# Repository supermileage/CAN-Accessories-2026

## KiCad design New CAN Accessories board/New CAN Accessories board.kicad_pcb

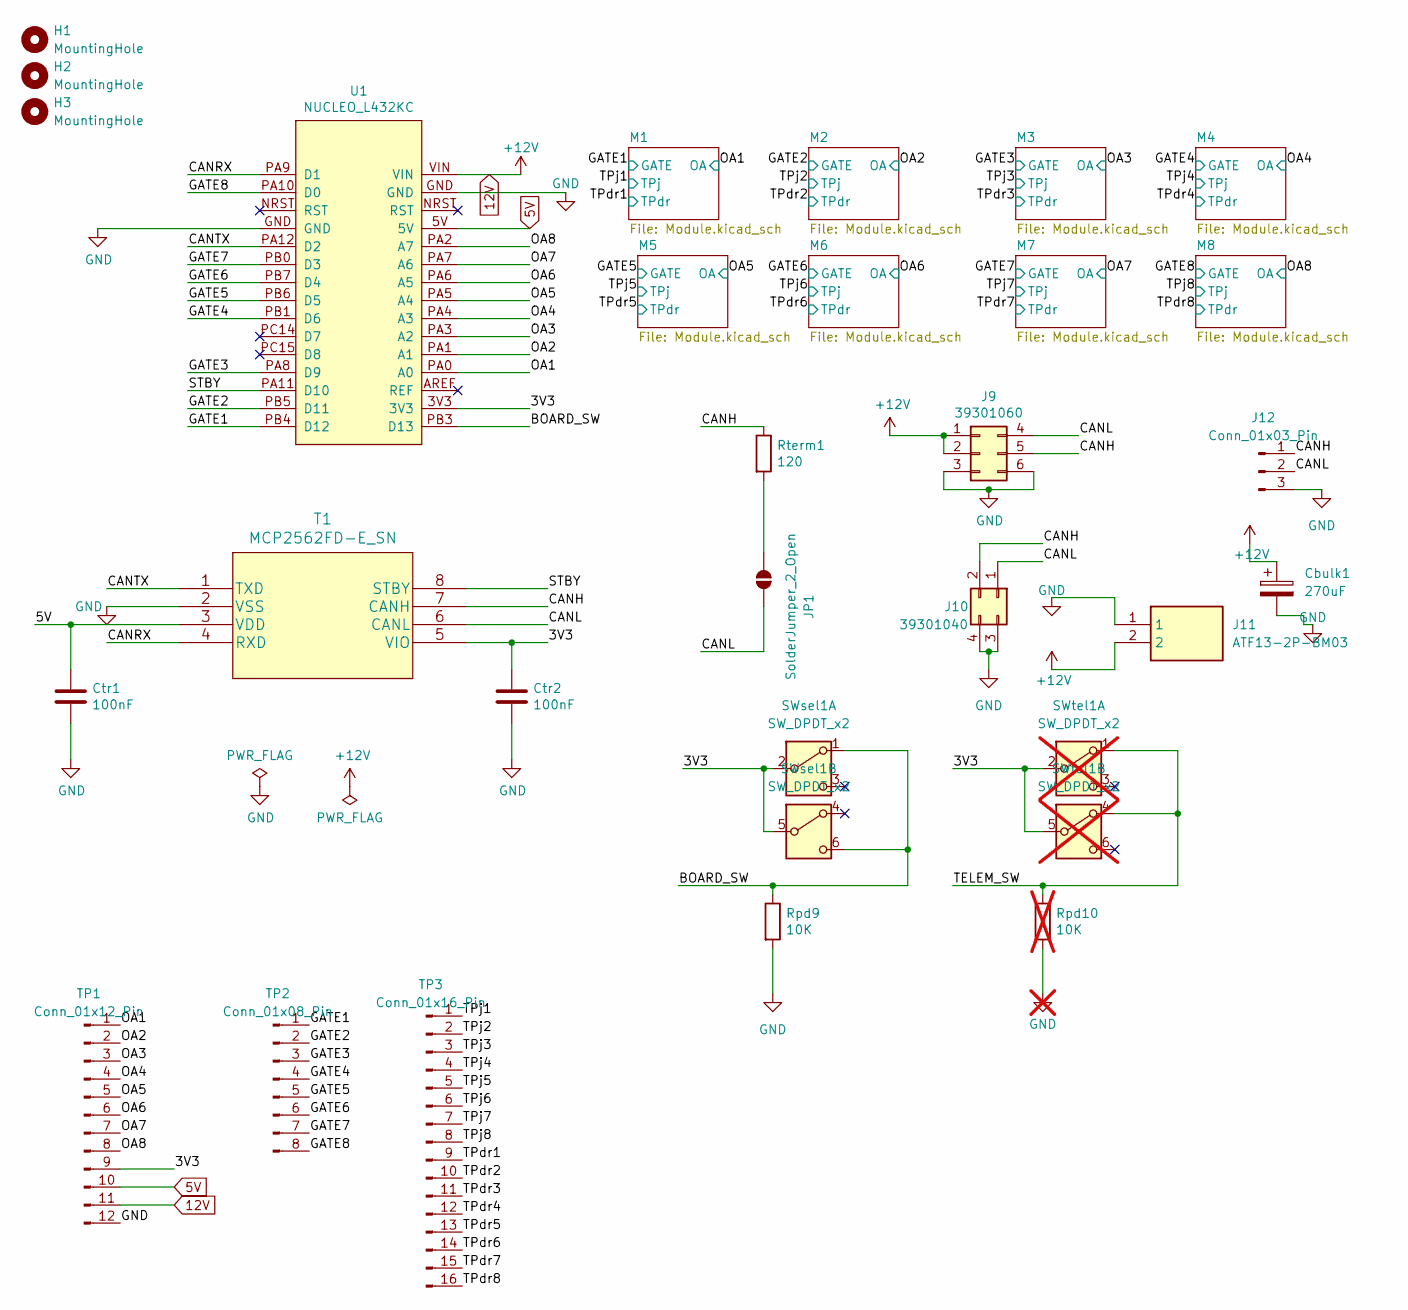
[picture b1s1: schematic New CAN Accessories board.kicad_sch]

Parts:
Cbulk1: 270uF; CAPAE1030X1050M
Ctr1, Ctr2: 100nF; C_0805_2012Metric
H1, H2, H3: MountingHole; MountingHole_3.2mm_M3_ISO14580
J9: 39301060; Molex_Mini-Fit_Jr_5569-06A2_2x03_P4.20mm_Horizontal
J10: 39301040; Molex_Mini-Fit_Jr_5569-04A2_2x02_P4.20mm_Horizontal
J11: ATF13-2P-BM03; ATF132PBM03; Mouser Part Number 654-ATF13-2P-BM03
J12: Conn_01x03_Pin; PinHeader_1x03_P2.54mm_Vertical
JP1: SolderJumper_2_Open; SolderJumper-2_P1.3mm_Open_Pad1.0x1.5mm
Rpd9: 10K; R_0805_2012Metric
Rpd10: 10K; R_0805_2012Metric; not fitted
Rterm1: 120; R_0805_2012Metric
SWsel1: SW_DPDT_x2; SWITCH_011CQN
SWtel1: SW_DPDT_x2; SWITCH_011CQN; not fitted
T1: MCP2562FD-E_SN; SOIC-8_3.9x4.9mm_P1.27mm
TP1: Conn_01x12_Pin; PinHeader_1x12_P2.54mm_Vertical
TP2: Conn_01x08_Pin; PinHeader_1x08_P2.54mm_Vertical
TP3: Conn_01x16_Pin; PinHeader_1x16_P2.54mm_Vertical
U1: NUCLEO_L432KC; MODULE_NUCLEO-L432KC

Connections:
5V: Ctr1.1, T1.3 (VDD), TP1.10, U1.5V; also elsewhere on the board
12V: Cbulk1.1, J9.1, J9.2, J11.2, TP1.11, U1.VIN; also elsewhere on the board
/3V3: Ctr2.1, SWsel1.2 (B), SWsel1.5 (B), SWtel1.2 (B), SWtel1.5 (B), T1.5 (VIO), TP1.9, U1.3V3
/BOARD_SW: Rpd9.1, SWsel1.1 (A), SWsel1.6 (C), U1.PB3 (D13)
/CANH: J9.5, J10.2, J12.1, Rterm1.1, T1.7 (CANH)
/CANL: J9.4, J10.1, J12.2, JP1.2 (B), T1.6 (CANL)
/CANRX: T1.4 (RXD), U1.PA9 (D1)
/CANTX: T1.1 (TXD), U1.PA12 (D2)
/GATE1: TP2.1, U1.PB4 (D12); also elsewhere on the board
/GATE2: TP2.2, U1.PB5 (D11); also elsewhere on the board
/GATE3: TP2.3, U1.PA8 (D9); also elsewhere on the board
/GATE4: TP2.4, U1.PB1 (D6); also elsewhere on the board
/GATE5: TP2.5, U1.PB6 (D5); also elsewhere on the board
/GATE6: TP2.6, U1.PB7 (D4); also elsewhere on the board
/GATE7: TP2.7, U1.PB0 (D3); also elsewhere on the board
/GATE8: TP2.8, U1.PA10 (D0); also elsewhere on the board
/OA1: TP1.1, U1.PA0 (A0); also elsewhere on the board
/OA2: TP1.2, U1.PA1 (A1); also elsewhere on the board
/OA3: TP1.3, U1.PA3 (A2); also elsewhere on the board
/OA4: TP1.4, U1.PA4 (A3); also elsewhere on the board
/OA5: TP1.5, U1.PA5 (A4); also elsewhere on the board
/OA6: TP1.6, U1.PA6 (A5); also elsewhere on the board
/OA7: TP1.7, U1.PA7 (A6); also elsewhere on the board
/OA8: TP1.8, U1.PA2 (A7); also elsewhere on the board
/STBY: T1.8 (STBY), U1.PA11 (D10)
/TPdr1: TP3.9; also elsewhere on the board
/TPdr2: TP3.10; also elsewhere on the board
/TPdr3: TP3.11; also elsewhere on the board
/TPdr4: TP3.12; also elsewhere on the board
/TPdr5: TP3.13; also elsewhere on the board
/TPdr6: TP3.14; also elsewhere on the board
/TPdr7: TP3.15; also elsewhere on the board
/TPdr8: TP3.16; also elsewhere on the board
/TPj1: TP3.1; also elsewhere on the board
/TPj2: TP3.2; also elsewhere on the board
/TPj3: TP3.3; also elsewhere on the board
/TPj4: TP3.4; also elsewhere on the board
/TPj5: TP3.5; also elsewhere on the board
/TPj6: TP3.6; also elsewhere on the board
/TPj7: TP3.7; also elsewhere on the board
/TPj8: TP3.8; also elsewhere on the board
GND: Cbulk1.2, Ctr1.2, Ctr2.2, J9.3, J9.6, J10.3, J10.4, J11.1, J12.3, Rpd9.2, Rpd10.2, T1.2 (VSS), TP1.12, U1.GND; also elsewhere on the board
unnamed: JP1.1 (A), Rterm1.2
unnamed: Rpd10.1, SWtel1.1 (A), SWtel1.4 (A)

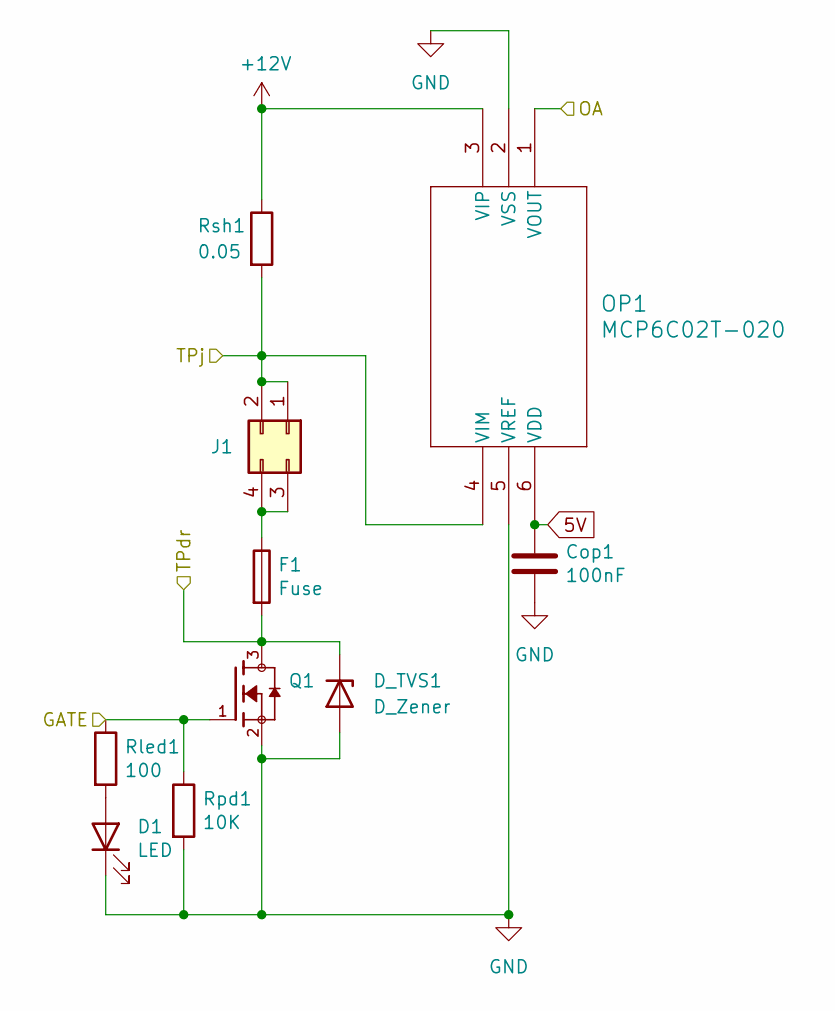
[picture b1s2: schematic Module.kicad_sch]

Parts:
Cop1: 100nF; C_0805_2012Metric
D1: LED; LED_0805_2012Metric
D_TVS1: D_Zener; D_SMF
F1: Fuse; 3586KTR
J1: 39301040; Molex_Mini-Fit_Jr_5569-04A2_2x02_P4.20mm_Horizontal
OP1: MCP6C02T-020; SOT-23-6_Handsoldering
Q1: IRLML6344TRPBF; TSOT-23; PARTREV December 19, 2014
Rled1: 100; R_0805_2012Metric
Rpd1: 10K; R_0805_2012Metric
Rsh1: 0.05; R_2512_6332Metric_Pad1.40x3.35mm_HandSolder

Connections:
5V: Cop1.1, OP1.6 (VDD); also elsewhere on the board
12V: OP1.3 (VIP), Rsh1.1; also elsewhere on the board
/GATE1: Q1.1, Rled1.1, Rpd1.1; also elsewhere on the board
/OA1: OP1.1 (VOUT); also elsewhere on the board
/TPdr1: D_TVS1.1 (K), F1.2, Q1.3; also elsewhere on the board
/TPj1: J1.1, J1.2, OP1.4 (VIM), Rsh1.2; also elsewhere on the board
GND: Cop1.2, D1.1 (K), D_TVS1.2 (A), OP1.2 (VSS), OP1.5 (VREF), Q1.2, Rpd1.2; also elsewhere on the board
unnamed: D1.2 (A), Rled1.2
unnamed: F1.1, J1.3, J1.4

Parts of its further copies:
Cop2, Cop3, Cop4, Cop5, Cop6, Cop7, Cop8: 100nF; C_0805_2012Metric
D2, D3, D4, D5, D6, D7, D8: LED; LED_0805_2012Metric
D_TVS2, D_TVS3, D_TVS4, D_TVS5, D_TVS6, D_TVS7, D_TVS8: D_Zener; D_SMF
F2, F3, F4, F5, F6, F7, F8: Fuse; 3586KTR
J2, J3, J4, J5, J6, J7, J8: 39301040; Molex_Mini-Fit_Jr_5569-04A2_2x02_P4.20mm_Horizontal
OP2, OP3, OP4, OP5, OP6, OP7, OP8: MCP6C02T-020; SOT-23-6_Handsoldering
Q2, Q3, Q4, Q5, Q6, Q7, Q8: IRLML6344TRPBF; TSOT-23; PARTREV December 19, 2014
Rled2, Rled3, Rled4, Rled5, Rled6, Rled7, Rled8: 100; R_0805_2012Metric
Rpd2, Rpd3, Rpd4, Rpd5, Rpd6, Rpd7, Rpd8: 10K; R_0805_2012Metric
Rsh2, Rsh3, Rsh4, Rsh5, Rsh6, Rsh7, Rsh8: 0.05; R_2512_6332Metric_Pad1.40x3.35mm_HandSolder

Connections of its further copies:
5V: Cop2.1, Cop3.1, Cop4.1, Cop5.1, Cop6.1, Cop7.1, Cop8.1, OP2.6 (VDD), OP3.6 (VDD), OP4.6 (VDD), OP5.6 (VDD), OP6.6 (VDD), OP7.6 (VDD), OP8.6 (VDD); also elsewhere on the board
12V: OP2.3 (VIP), OP3.3 (VIP), OP4.3 (VIP), OP5.3 (VIP), OP6.3 (VIP), OP7.3 (VIP), OP8.3 (VIP), Rsh2.1, Rsh3.1, Rsh4.1, Rsh5.1, Rsh6.1, Rsh7.1, Rsh8.1; also elsewhere on the board
/GATE2: Q2.1, Rled2.1, Rpd2.1; also elsewhere on the board
/GATE3: Q3.1, Rled3.1, Rpd3.1; also elsewhere on the board
/GATE4: Q4.1, Rled4.1, Rpd4.1; also elsewhere on the board
/GATE5: Q5.1, Rled5.1, Rpd5.1; also elsewhere on the board
/GATE6: Q6.1, Rled6.1, Rpd6.1; also elsewhere on the board
/GATE7: Q7.1, Rled7.1, Rpd7.1; also elsewhere on the board
/GATE8: Q8.1, Rled8.1, Rpd8.1; also elsewhere on the board
/OA2: OP2.1 (VOUT); also elsewhere on the board
/OA3: OP3.1 (VOUT); also elsewhere on the board
/OA4: OP4.1 (VOUT); also elsewhere on the board
/OA5: OP5.1 (VOUT); also elsewhere on the board
/OA6: OP6.1 (VOUT); also elsewhere on the board
/OA7: OP7.1 (VOUT); also elsewhere on the board
/OA8: OP8.1 (VOUT); also elsewhere on the board
/TPdr2: D_TVS2.1 (K), F2.2, Q2.3; also elsewhere on the board
/TPdr3: D_TVS3.1 (K), F3.2, Q3.3; also elsewhere on the board
/TPdr4: D_TVS4.1 (K), F4.2, Q4.3; also elsewhere on the board
/TPdr5: D_TVS5.1 (K), F5.2, Q5.3; also elsewhere on the board
/TPdr6: D_TVS6.1 (K), F6.2, Q6.3; also elsewhere on the board
/TPdr7: D_TVS7.1 (K), F7.2, Q7.3; also elsewhere on the board
/TPdr8: D_TVS8.1 (K), F8.2, Q8.3; also elsewhere on the board
/TPj2: J2.1, J2.2, OP2.4 (VIM), Rsh2.2; also elsewhere on the board
/TPj3: J3.1, J3.2, OP3.4 (VIM), Rsh3.2; also elsewhere on the board
/TPj4: J4.1, J4.2, OP4.4 (VIM), Rsh4.2; also elsewhere on the board
/TPj5: J5.1, J5.2, OP5.4 (VIM), Rsh5.2; also elsewhere on the board
/TPj6: J6.1, J6.2, OP6.4 (VIM), Rsh6.2; also elsewhere on the board
/TPj7: J7.1, J7.2, OP7.4 (VIM), Rsh7.2; also elsewhere on the board
/TPj8: J8.1, J8.2, OP8.4 (VIM), Rsh8.2; also elsewhere on the board
GND: Cop2.2, Cop3.2, Cop4.2, Cop5.2, Cop6.2, Cop7.2, Cop8.2, D2.1 (K), D3.1 (K), D4.1 (K), D5.1 (K), D6.1 (K), D7.1 (K), D8.1 (K), D_TVS2.2 (A), D_TVS3.2 (A), D_TVS4.2 (A), D_TVS5.2 (A), D_TVS6.2 (A), D_TVS7.2 (A), D_TVS8.2 (A), OP2.2 (VSS), OP2.5 (VREF), OP3.2 (VSS), OP3.5 (VREF), OP4.2 (VSS), OP4.5 (VREF), OP5.2 (VSS), OP5.5 (VREF), OP6.2 (VSS), OP6.5 (VREF), OP7.2 (VSS), OP7.5 (VREF), OP8.2 (VSS), OP8.5 (VREF), Q2.2, Q3.2, Q4.2, Q5.2, Q6.2, Q7.2, Q8.2, Rpd2.2, Rpd3.2, Rpd4.2, Rpd5.2, Rpd6.2, Rpd7.2, Rpd8.2; also elsewhere on the board
unnamed: D2.2 (A), Rled2.2
unnamed: D3.2 (A), Rled3.2
unnamed: D4.2 (A), Rled4.2
unnamed: D5.2 (A), Rled5.2
unnamed: D6.2 (A), Rled6.2
unnamed: D7.2 (A), Rled7.2
unnamed: D8.2 (A), Rled8.2
unnamed: F2.1, J2.3, J2.4
unnamed: F3.1, J3.3, J3.4
unnamed: F4.1, J4.3, J4.4
unnamed: F5.1, J5.3, J5.4
unnamed: F6.1, J6.3, J6.4
unnamed: F7.1, J7.3, J7.4
unnamed: F8.1, J8.3, J8.4

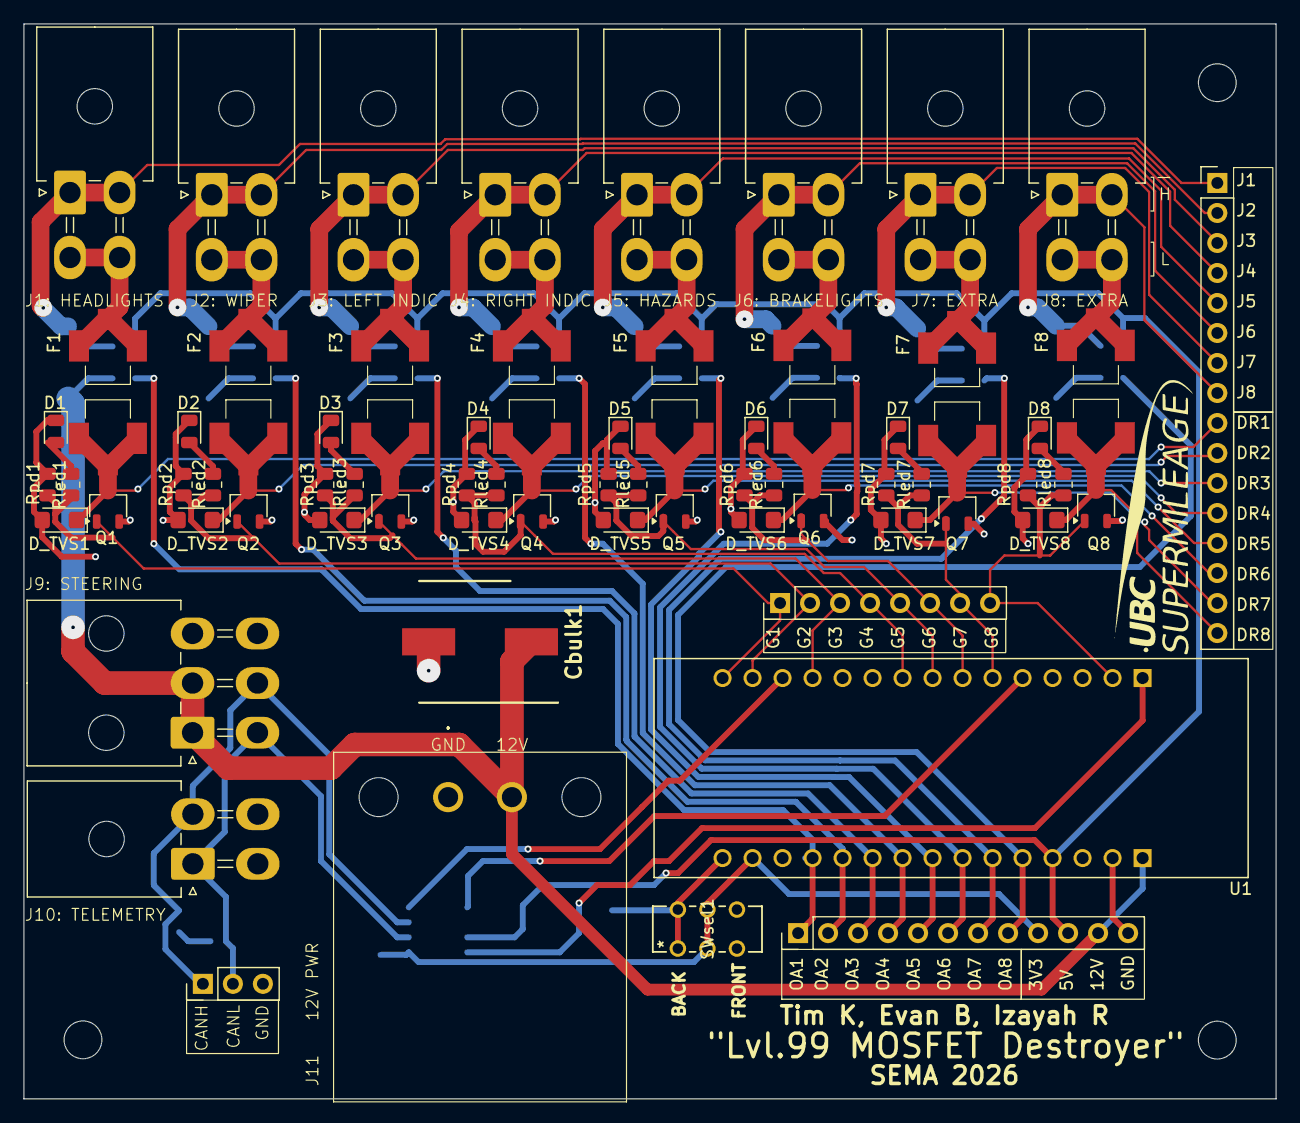
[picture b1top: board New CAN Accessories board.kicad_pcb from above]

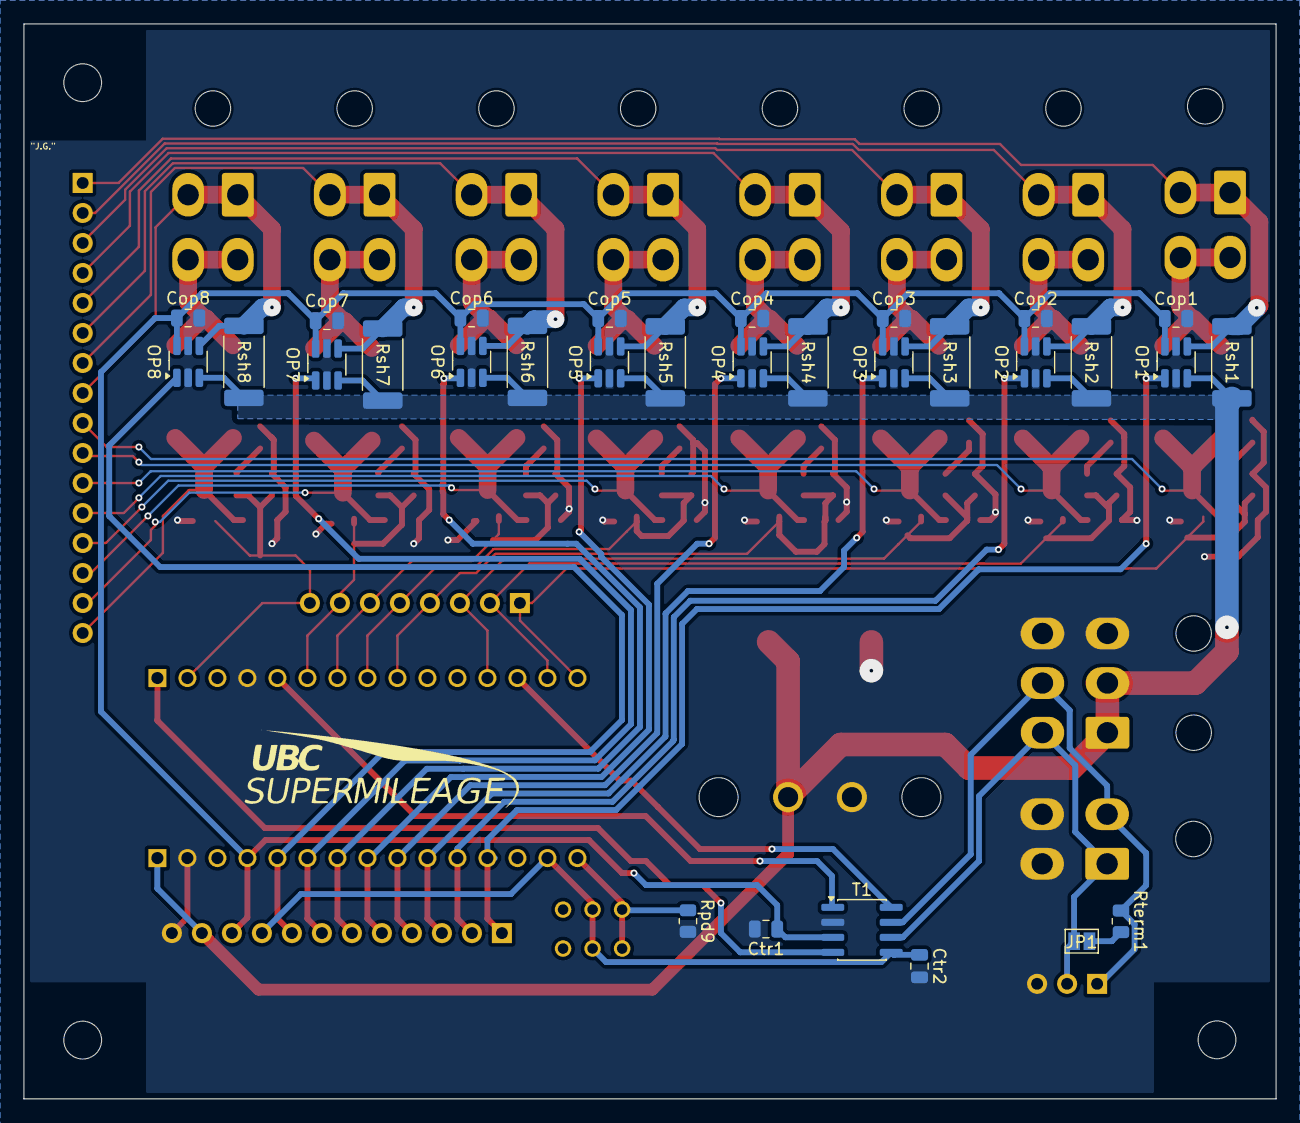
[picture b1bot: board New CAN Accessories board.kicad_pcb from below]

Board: 2 copper layers, 106.0 x 91.0 mm, 99 parts (30 on the bottom side), 59 nets.

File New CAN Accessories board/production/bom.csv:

Designator,Footprint,Quantity,Value,LCSC Part #
CBULK1,CAPAE1030X1050M,1,270uF,
"COP1, COP2, COP3, COP4, COP5, COP6, COP7, COP8, CTR1, CTR2",0805,10,100nF,
"D1, D2, D3, D4, D5, D6, D7, D8",0805,8,LED,
"D_TVS1, D_TVS2, D_TVS3, D_TVS4, D_TVS5, D_TVS6, D_TVS7, D_TVS8",D_SMF,8,D_Zener,
"F1, F2, F3, F4, F5, F6, F7, F8",3586KTR,8,Fuse,
"J1, J10, J2, J3, J4, J5, J6, J7, J8",Molex_Mini-Fit_Jr_5569-04A2_2x02_P4.20mm_Horizontal,9,39301040,
J11,ATF132PBM03,1,ATF13-2P-BM03,
J12,PinHeader_1x03_P2.54mm_Vertical,1,Conn_01x03_Pin,
J9,Molex_Mini-Fit_Jr_5569-06A2_2x03_P4.20mm_Horizontal,1,39301060,
JP1,SolderJumper-2_P1.3mm_Open_Pad1.0x1.5mm,1,SolderJumper_2_Open,
"OP1, OP2, OP3, OP4, OP5, OP6, OP7, OP8",SOT-23-6_Handsoldering,8,MCP6C02T-020,
"Q1, Q2, Q3, Q4, Q5, Q6, Q7, Q8",TSOT-23,8,IRLML6344TRPBF,
"RLED1, RLED2, RLED3, RLED4, RLED5, RLED6, RLED7, RLED8",0805,8,100,
"RPD1, RPD2, RPD3, RPD4, RPD5, RPD6, RPD7, RPD8, RPD9",0805,9,10K,
"RSH1, RSH2, RSH3, RSH4, RSH5, RSH6, RSH7, RSH8",2512,8,0.05,
RTERM1,0805,1,120,
SWSEL1,SWITCH_011CQN,1,SW_DPDT_x2,
T1,SOIC-8_3.9x4.9mm_P1.27mm,1,MCP2562FD-E_SN,
TP1,PinHeader_1x12_P2.54mm_Vertical,1,Conn_01x12_Pin,
TP2,PinHeader_1x08_P2.54mm_Vertical,1,Conn_01x08_Pin,
TP3,PinHeader_1x16_P2.54mm_Vertical,1,Conn_01x16_Pin,
U1,MODULE_NUCLEO-L432KC,1,NUCLEO_L432KC,

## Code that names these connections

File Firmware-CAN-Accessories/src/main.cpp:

#include "mbed.h"
#include <iostream>
//#include <CAN.h>
#include <vector>
#include "accessory.h"
#include <chrono>

using std::string;

//CAN CONNECTIONS
#define CAN_TX PA_12
#define CAN_RX PA_11
#define CAN_STBY PA_9

//Gates
#define GATE1 PB_4
#define GATE2 PB_5  
#define GATE3 PA_8
#define GATE4 PB_1
#define GATE5 PB_6
#define GATE6 PB_7
#define GATE7 PB_0
#define GATE8 PA_10

//Current Sense Op amp output pins
#define OA1 PA_0
#define OA2 PA_1
#define OA3 PA_3
#define OA4 PA_4
#define OA5 PA_5
#define OA6 PA_6
#define OA7 PA_7
#define OA8 PA_2 //this disables serial communication.

//Board Switch
#define SWITCH PB_3

//Front and Back boards
#define FRONT 0
#define BACK 1
#define BOTH 2

//CAN
#define BAUD_RATE 500000
#define CAN_FORMAT 0x60
CAN can(CAN_RX, CAN_TX, BAUD_RATE);

//ADC
#define vref 3.3
#define op_amp_gain 20
#define r_shunt 0.05

// //Telemetry
// Ticker telem_ticker;
// volatile bool send_telem_flag = false;

// void set_telem_flag() {
//     send_telem_flag = true;
// }

// void send_telem_message(std::vector<Accessory*> totalAccList, CANMessage telem_msg) {
//     telem_msg.len = 4;
//     for(int i = 0; i < totalAccList.size(); i++) {
//         telem_msg.id = i;
//         float raw_adc = (*totalAccList[i]).get_i_sense();
//         int32_t encoded = (int32_t)round(raw_adc * 1000);

//         telem_msg.data[0] = (encoded >> 24) & 0xFF;
//         telem_msg.data[1] = (encoded >> 16) & 0xFF;
//         telem_msg.data[2] = (encoded >> 8)  & 0xFF;
//         telem_msg.data[3] = encoded & 0xFF;
//         //float current_draw = (raw_adc*vref)/(op_amp_gain*r_shunt*1000.0f); //in milli-amps


//         // if (current_draw < 0) {
//         //     current_draw = 0;
//         // }
//         // if (current_draw > 255) {
//         //     current_draw = 255;
//         // }
//         //telem_msg.data[i] = (uint8_t)current_draw; //currently can only communiate in range 0-255mA, will fix
//         can.write(telem_msg);
//     }
// }


int main(){
//Declare all Accessories
//Gate,Opamp,Board,Name,InitialState,Blinks

Accessory idleLights    (GATE1, OA1, BACK, "idleLights"  , 0, 0);// id6
Accessory headlights    (GATE1, OA1, FRONT, "headlights" , 0, 0);// id0
Accessory wiper         (GATE2, OA2, FRONT, "wiper"      , 0, 0);// id1
Accessory leftIndic     (GATE3, OA3, BOTH , "leftIndic"  , 1, 1);// id2
Accessory rightIndic    (GATE4, OA4, BOTH , "rightIndic" , 1, 1);// id3
Accessory horn          (GATE7, OA5, FRONT, "horn"       , 0, 0);// id4
Accessory brakelights   (GATE6, OA6, BACK , "brakelights", 1, 0);// id5

//Pointer because you cant copy accesory type
std::vector<Accessory*>totalAccList= {&headlights, &wiper, &leftIndic, &rightIndic, &horn, &brakelights, &idleLights};


//Declare board switch pin
DigitalIn boardSwitch(SWITCH);

/*
std::vector<Accessory*>totalAccList;
if(boardSwitch.read()) std::vector<Accessory*>totalAccList = totalAccListFront;
else                   std::vector<Accessory*>totalAccList = totalAccListBack;
*/

int accAmount = totalAccList.size();

//Initialize CAN
DigitalOut canStby(CAN_STBY);
//disable CAN standby
canStby=0;
CANMessage msg;
// CANMessage telem_msg;
// if (boardSwitch.read()) {
//     telem_ticker.attach(callback(&set_telem_flag), TELEM_RATE);
// }
//telem_ticker.attach(callback([&]() {send_telem_message(totalAccList, telem_msg);}), TELEM_RATE); STM DID NOT LIKE THIS

bool nextState;

while(true) {
    // if(send_telem_flag) {
    //         send_telem_flag = false;
    //         send_telem_message(totalAccList, telem_msg);
    //     }

    //Process messages
    if(can.read(msg) && msg.id == CAN_FORMAT)
    {
        switch(msg.data[0])
        {
    
            //IOPERATION MODE 0: Set status of all accessories at once
            case 0: 
                for(int j = 0; j < accAmount; j++)
                {
                    bool nextState = (msg.data[1] >> j) & 1;
                    
                    if((totalAccList[j])->board == boardSwitch.read() || (totalAccList[j]->board == BOTH)){
                        (*(totalAccList[j])).updateState(nextState);
                    }
                }
                
            break;

            //OPERATION MODE 2: turn individual accessories on and off.
            case 2:
                
                for(int j = 1; j < msg.len; j++)
                {
                    bool nextState = (msg.data[j] & 1);
                    int acc = msg.data[j] >> 1;
                    
                    if(totalAccList[acc]->board == boardSwitch.read() || totalAccList[acc]->board == BOTH){
                        (*(totalAccList[acc])).updateState(nextState);
                    }
                }
        }
    }

} 

}

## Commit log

2025-09-27 created new kicad project file
2025-09-30 updated schematic to add high side sensing, haven't speced specific components yet
2025-10-05 updated kicad schematic to include new op amps and update layout
2025-10-05 updated schematic again, all parts match bom, for final review
2025-10-09 deleted 3 outside connectors
2025-10-09 Changed switch symbols
2025-10-11 Footprints updated
2025-10-12 Added decoupling caps on opamps, improved part designator labelling and naming
2025-10-16 split J10 into 2pin 12V connector and 4pin can connector
2025-10-16 Annotate
2025-10-17 preliminary layout complete
2025-10-18 added test points in schematic
2025-10-18 added 3d models
2025-10-18 post design review
2025-10-18 Added test points 1x12 pin and 1x8 pin
2025-10-19 added bulk cap
2025-10-19 Added two 1x4 pin headers for J1-J8 - also fixed CAN module
2025-10-20 few labelling changes
2025-10-20 added labellling changes noted in design review
2025-10-20 very minor positioning and labelling changes
2025-10-20 I think i resolved the merge conflict, should be evan's changes + tim's small changes
2025-10-20 resolve merge conflict
2025-10-22 added supermileage logo and names
2025-10-22 added TVS diode to schematic
2025-10-22 named tvs diode correctly
2025-10-22 hmmm
2025-10-23 started making drain test point changes
2025-10-23 1x16 header test points
2025-10-24 TVS Diode added
2025-10-24 Silk screen fixes
2025-10-24 Removed redundant trace
2025-10-24 Fixed rled 6 silkscreen
2025-10-24 updated diode placement
2025-10-24 finalized PCB design
2025-10-24 final final design (changed a couple traces)
2025-10-27 PCB enclosure v1, and PlatformIO project created
2025-11-03 first pass at firmware
2025-11-20 updated accessory.cpp to be up to date
2025-11-20 Izayah main changes accessory header
2025-11-20 starting new branch
2025-11-20 syntax fixes
2025-11-22 updated to main
2025-11-22 updated firmware
2025-11-22 put in op amp pins and fixed build issues
2025-11-22 Case 0 Implementation
2025-11-29 post solder bridge fix
2025-11-29 combining current sensing and all cases
2025-11-29 fixed cpp dupe error
2025-11-29 fixed dupe error
2025-11-29 cleaned up code
2025-11-30 fixed acc.cpp merge conflict
2025-11-30 Uploaded recent changes
2025-12-03 Recent Changes
2025-12-04 added telemetry
2025-12-04 added telemetry and comments
2025-12-05 Cleaned up code and fixed front vs. back acc implementation
2025-12-05 more cleanup
2025-12-05 brief telemetry changes
2025-12-05 standardized variable naming format
2025-12-05 updated telemetry
2025-12-05 small telem changes
2025-12-06 fixing telemetry still
2025-12-06 fixed telemetry
2025-12-06 labelled broken ADC
2025-12-06 minor telemetry changes
2025-12-06 more minor telemetry changes
2025-12-06 merged evan branch with main to add telemetry
2026-01-06 telemetry added, fixed blinking led3
2026-02-01 switched horn gate from gate 5 to gate 7, commented out all telemetry code
2026-02-03 Added Idle Lights accessory
